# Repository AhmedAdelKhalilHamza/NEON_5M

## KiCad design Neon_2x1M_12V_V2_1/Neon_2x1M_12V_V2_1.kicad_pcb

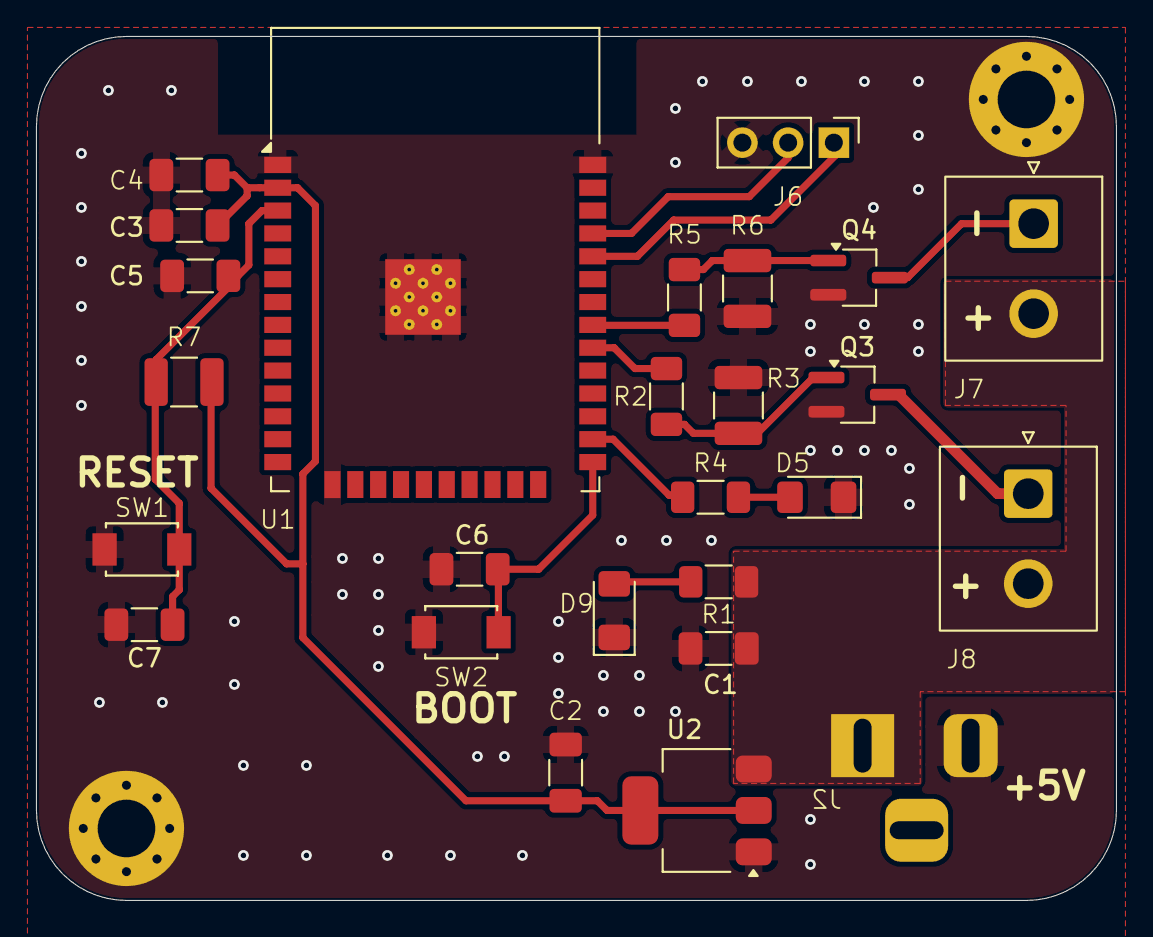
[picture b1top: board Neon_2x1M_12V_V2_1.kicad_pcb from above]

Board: 2 copper layers, 60.0 x 48.0 mm, 28 parts (1 on the bottom side), 16 nets.

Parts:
C1, C2, C3: 22uF/10V(20%); C_1206_3216Metric_Pad1.33x1.80mm_HandSolder
C4, C5, C6, C7: 0.1uF/50V(10%); C_1206_3216Metric_Pad1.33x1.80mm_HandSolder
D5: Blue Indicator LED; LED_1206_3216Metric_Pad1.42x1.75mm_HandSolder
D9: Red Power LED; LED_1206_3216Metric_Pad1.42x1.75mm_HandSolder
H1, H4: MountingHole_Pad; MountingHole_3.2mm_M3_Pad_Via
J2: Barrel_Jack_MountingPin; BarrelJack_Horizontal
J6: Conn_01x03_Pin; PinHeader_1x03_P2.54mm_Vertical
J7, J8: Screw_Terminal_01x02; JST_NV_B02P-NV_1x02_P5.00mm_Vertical
Q3, Q4: AO3400A; TSOT-23_HandSoldering
R1: 2K(5%); R_1206_3216Metric_Pad1.30x1.75mm_HandSolder
R2, R5: 100 Ohm; R_1206_3216Metric_Pad1.30x1.75mm_HandSolder
R3, R6, R7: 10k; R_1210_3225Metric_Pad1.30x2.65mm_HandSolder
R4: 1K; R_1206_3216Metric_Pad1.30x1.75mm_HandSolder
SW1, SW2: SW_Push; TS_button_3_4_2
U1: ESP32-WROOM-32
U2: AMS1117-3.3; SOT-223-3_TabPin2

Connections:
+3V3: C2.1, C3.1, C4.1, R7.1, U1.2 (VDD), U2.2 (VO)
+5V: C1.1, J2.1, J7.2, J8.2, R1.2, U2.3 (VI)
B_Jack: J8.1, Q3.3 (D)
ESP_EN: C5.1, C7.1, R7.2, SW1.2, U1.3 (EN)
ESP_IO0: C6.1, SW2.2, U1.25 (IO0)
ESP_IO4: R4.2, U1.26 (IO4)
ESP_IO18: R2.2, U1.30 (IO18)
ESP_IO19: R5.2, U1.31 (IO19)
ESP_U0RX: J6.1, U1.34 (RXD0/IO3)
ESP_U0TX: J6.2, U1.35 (TXD0/IO1)
GND: C1.2, C2.2, C3.2, C4.2, C5.2, C6.2, C7.2, D5.1 (K), D9.1 (K), H1.1 (1_1), H4.1 (1_1), J2.2, J6.3, Q3.2 (S), Q4.2 (S), R3.2, R6.2, SW1.1, SW2.1, U1.1 (GND), U1.15 (GND), U1.38 (GND), U1.39 (GND), U2.1 (GND)
unnamed: D5.2 (A), R4.1
unnamed: D9.2 (A), R1.1
unnamed: Q3.1 (G), R2.1, R3.1
unnamed: Q4.1 (G), R5.1, R6.1
P_Jack: J7.1, Q4.3 (D)

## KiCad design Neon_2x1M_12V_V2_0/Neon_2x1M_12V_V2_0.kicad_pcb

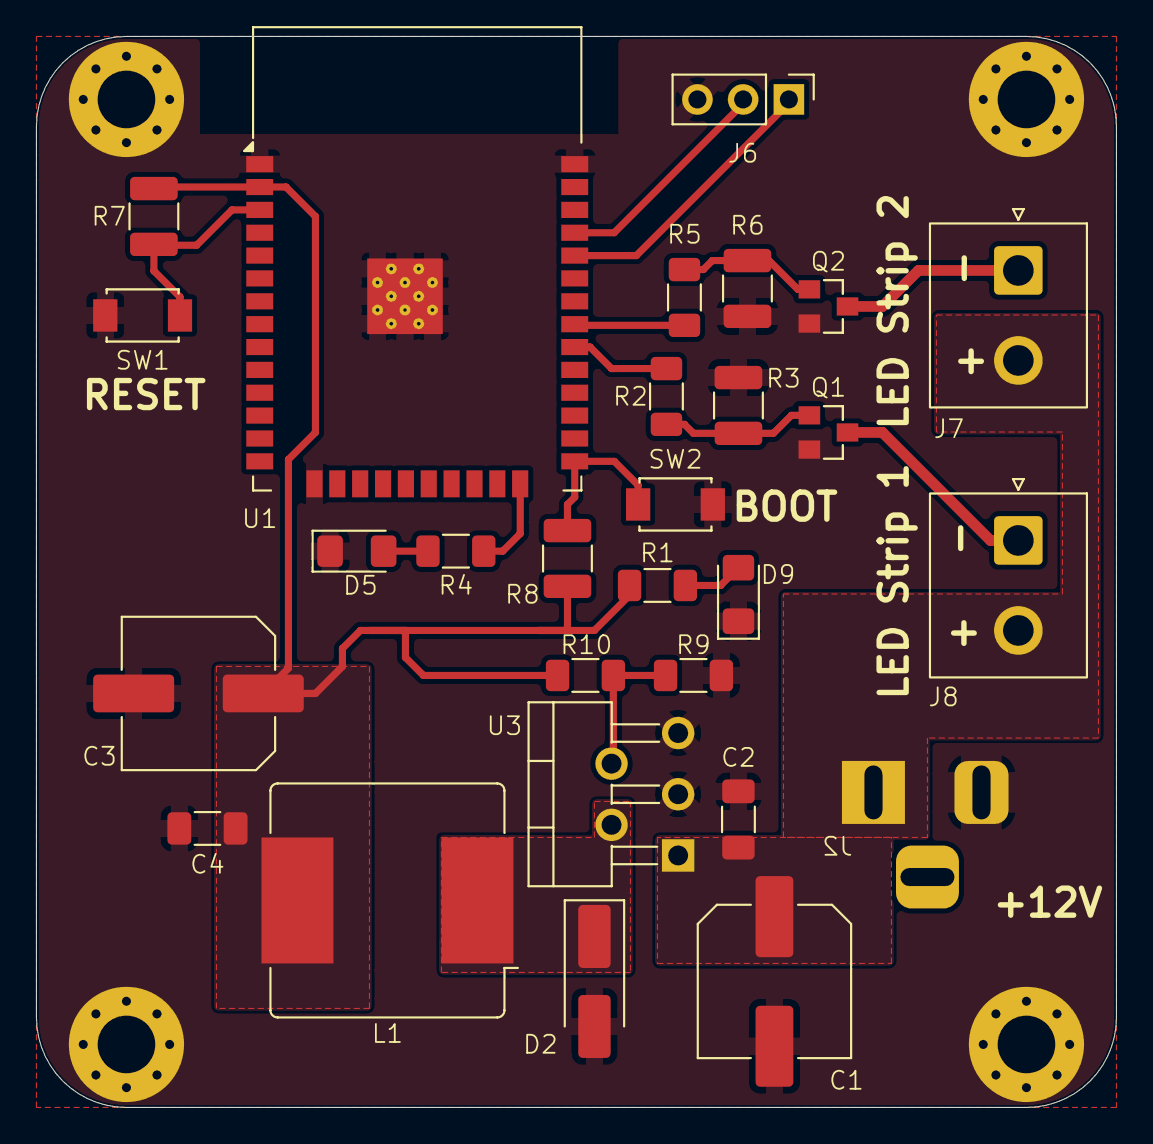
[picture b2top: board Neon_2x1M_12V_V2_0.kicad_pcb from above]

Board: 2 copper layers, 60.0 x 59.5 mm, 32 parts (1 on the bottom side), 18 nets.

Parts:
C1: 100uF; C_Elec_8x10.2
C2, C4: 100nF; C_1206_3216Metric_Pad1.33x1.80mm_HandSolder
C3: 220uF; C_Elec_8x10.2
D2: SS34; D_SMA_Handsoldering
D5: Blue Indicator LED; LED_1206_3216Metric_Pad1.42x1.75mm_HandSolder
D9: Red Power LED; LED_1206_3216Metric_Pad1.42x1.75mm_HandSolder
H1, H2, H3, H4: MountingHole_Pad; MountingHole_3.2mm_M3_Pad_Via
J2: Barrel_Jack_MountingPin; BarrelJack_Horizontal
J6: Conn_01x03_Pin; PinHeader_1x03_P2.54mm_Vertical
J7, J8: Screw_Terminal_01x02; JST_NV_B02P-NV_1x02_P5.00mm_Vertical
L1: 47uH; L_Bourns_SRR1208_12.7x12.7mm
Q1, Q2: IRLML2502TRPBF; custom_SOT23
R1, R4: 820 Ohm; R_1206_3216Metric_Pad1.30x1.75mm_HandSolder
R2, R5: 100 Ohm; R_1206_3216Metric_Pad1.30x1.75mm_HandSolder
R3, R6, R7, R8: 10k Ohm; R_1210_3225Metric_Pad1.30x2.65mm_HandSolder
R9: 16K; R_1206_3216Metric_Pad1.30x1.75mm_HandSolder
R10: 27K; R_1206_3216Metric_Pad1.30x1.75mm_HandSolder
SW1, SW2: SW_Push; TS_button_3_4_2
U1: ESP32-WROOM-32
U3: LM2596T-ADJ; TO-220-5_P3.4x3.7mm_StaggerOdd_Lead3.8mm_Vertical

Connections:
+3V3: C3.1, C4.1, L1.2, R1.2, R7.2, R8.2, R10.1, U1.2 (VDD)
+12V: C1.1, C2.1, J2.1, J7.2, J8.2, U3.1 (VIN)
/BUCK_SW: D2.1 (K), L1.1, U3.2 (OUT)
B_Jack: J8.1, Q1.3 (D)
ESP_EN: R7.1, SW1.2, U1.3 (EN)
ESP_IO0: R8.1, SW2.2, U1.25 (IO0)
ESP_IO2: R4.2, U1.24 (IO2)
ESP_IO18: R2.2, U1.30 (IO18)
ESP_IO19: R5.2, U1.31 (IO19)
ESP_U0RX: J6.1, U1.34 (RXD0/IO3)
ESP_U0TX: J6.2, U1.35 (TXD0/IO1)
GND: C1.2, C2.2, C3.2, C4.2, D2.2 (A), D5.1 (K), D9.1 (K), H1.1 (1_1), H2.1 (1_1), H3.1 (1_1), H4.1 (1_1), J2.2, J6.3, Q1.2 (S), Q2.2 (S), R3.2, R6.2, R9.2, SW1.1, SW2.1, U1.1 (GND), U1.15 (GND), U1.38 (GND), U1.39 (GND), U3.3 (GND), U3.5 (~ON/OFF)
unnamed: D5.2 (A), R4.1
unnamed: D9.2 (A), R1.1
unnamed: Q1.1 (G), R2.1, R3.1
unnamed: Q2.1 (G), R5.1, R6.1
unnamed: R9.1, R10.2, U3.4 (FB)
P_Jack: J7.1, Q2.3 (D)

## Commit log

2025-11-03 updated RGB 5mm led current sensing resistors values for 12v supply on anode
2025-11-03 updated errors
2025-11-04 exported footprint to layout
2025-11-04 updated esp32 footprint keepout zone
2025-11-06 update b.silkscreen text
2025-11-06 updated esp32 keepout zone for antena
2025-11-07 added custom sot23 foorprint and 3d model
2025-11-08 updated project name
2025-11-08 updated project name backup files
2025-11-08 updated jst connector placement
2025-11-08 updated switching pin (3) the mounting pin to be unconnected as it is not important
2025-11-08 added vias to 12v routes
2025-11-08 generated BOM
2025-11-09 updated components checklist
2025-11-11 generated production files
2026-04-06 initial commit remove old chinese buck converter and replace it with LM2596 DC DC converter adjustable
2026-04-11 updated file names and deleted not needed folders
2026-04-13 updated schematic and layout for V2.0
2026-04-13 updated placement, routing and added final touches
2026-04-13 updated BOM and generated BOM csv file also updated schematic and layout along
2026-04-14 updated production files and updated connectors orientation to match 1 layer pcb manufacturing as connectors flipped
2026-04-14 updated production files
2026-04-14 updated layout and regenerated gerbers for manufacturer
2026-04-21 completed BOM in hand revision
2026-04-30 updated schematic to change input voltage from 12v to 5v
2026-05-01 updated ERC
2026-05-01 updated schematic and footprints
2026-05-02 updated PCB layout
